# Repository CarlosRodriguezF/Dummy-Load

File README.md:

# Dummy-Load
Dummy-Load with Digital Control

V1.1
-----------------
1. Serie Resistor on MOSFET GATE to prevent oscillators.
2. NEW OPAMP RailtoRail DUAL, LMC662
3. New desing of PCB

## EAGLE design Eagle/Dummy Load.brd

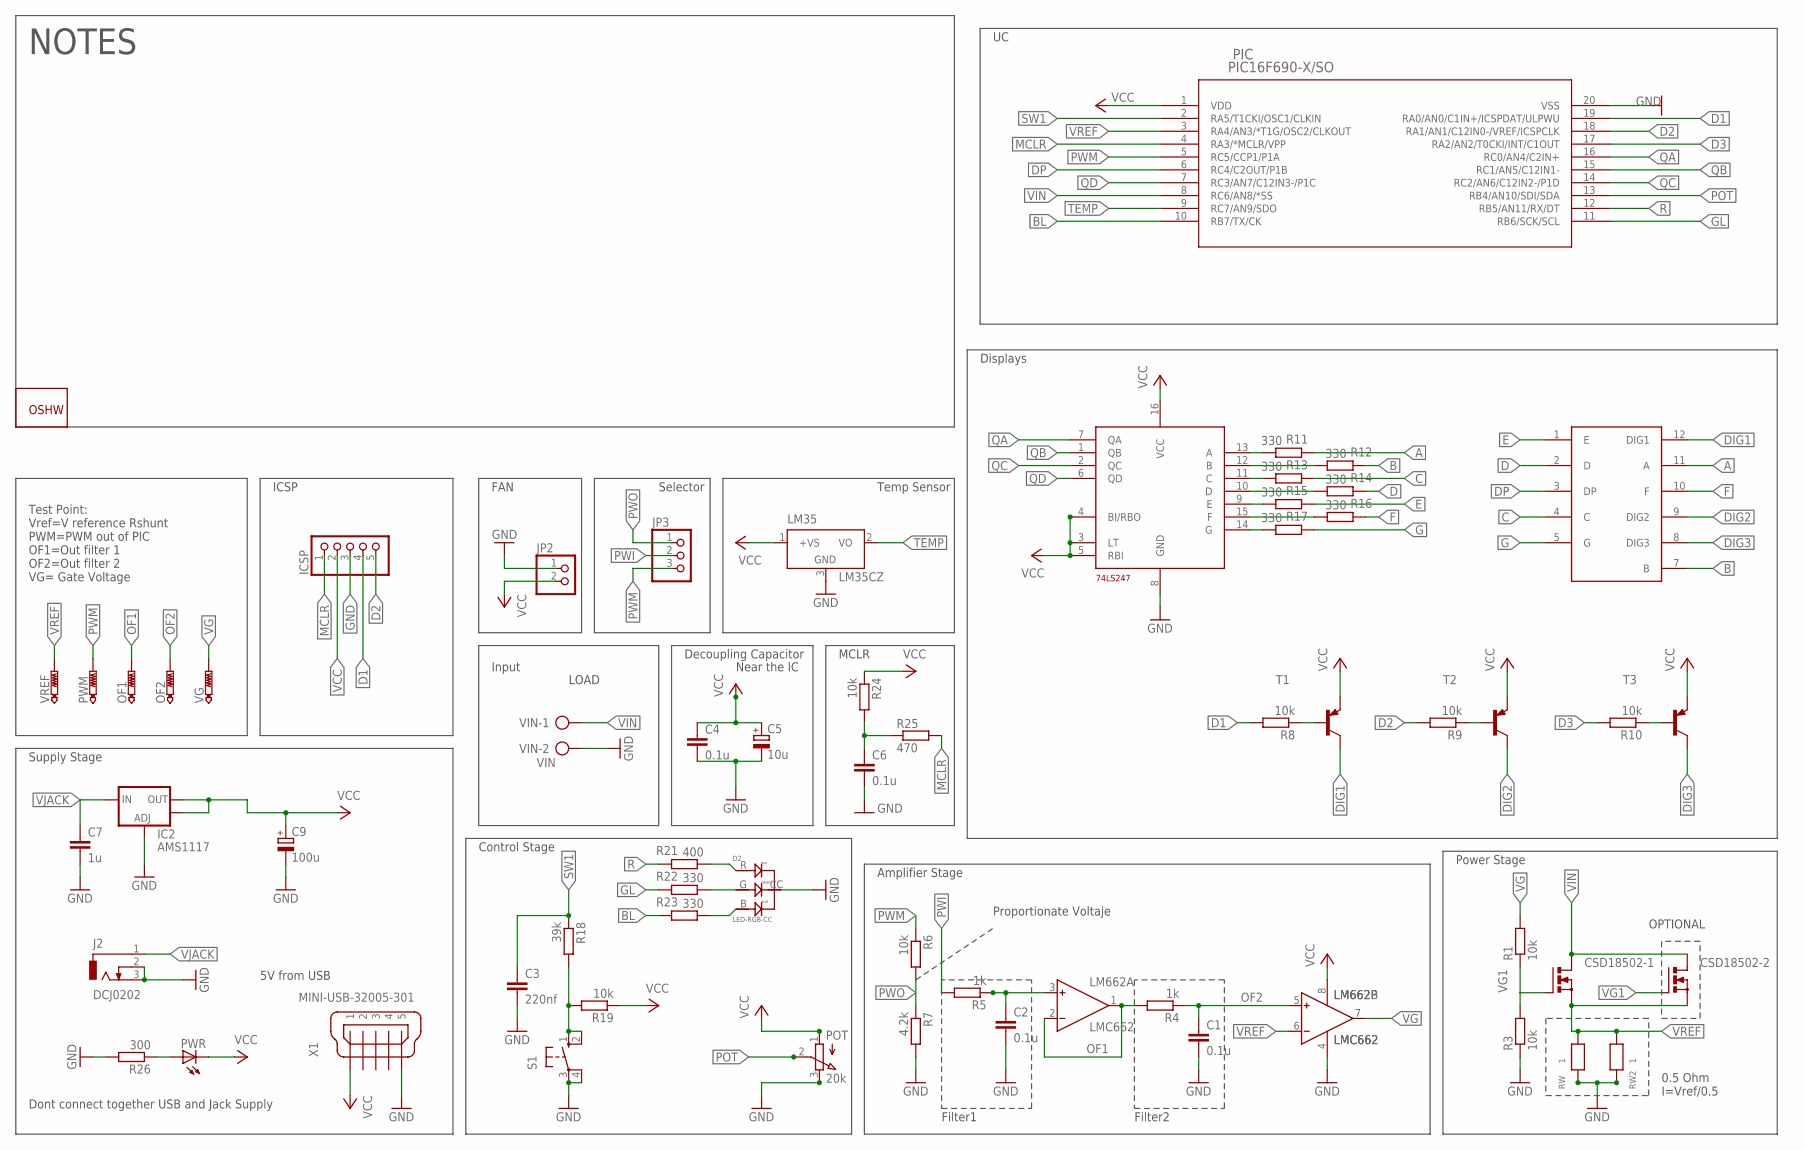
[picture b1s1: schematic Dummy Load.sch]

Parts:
74LS247: BCD-7; SOIC-16
C1, C2, C4, C6: 0.1u; C0805
C3: 220nf; C0805
C5: 10u; 153CLV-0405
C7: 1u; C0805
C9: 100u; 153CLV-0605
CSD18502-1, CSD18502-2: PMOSFET_NTO220BV; TO220BV
D2: LED-RGB-CC
DISPLAY: 7-SEGMENT--DIGITS
GOLD_ORB_SM2: OSHWLOGO_GOLD_ORB_MED; OSHW1
IC2: AMS1117; SOT223
ICSP: PINHD-1X5; 1X05
J2: DCJ0202
JP2: PINHD-1X2; 1X02
JP3: PINHD-1X3; 1X03
LM35: LM35CZ; TO92
LM662: LMC662; SO8
OF1, OF2: PTR1B1,27; B1,27
PIC: PIC16F690-X/SO; SOIC20-W_MC
POT: 20k; 3RP/1610N
PWM: PTR1B1,27; B1,27
PWR: LEDCHIP-LED0805; CHIP-LED0805
R1, R3, R6, R8, R9, R10, R19, R24: 10k; R0805
R4, R5: 1k; R0805
R7: 4.2k; R0805
R11, R12, R13, R14, R15, R16, R17, R22, R23: 330; R0805
R18: 39k; R0805
R21: 400; R0805
R25: 470; R0805
R26: 300; R0805
RW, RW2: 1; RESISTOR5W
S1: 10-XX; B3F-10XX
T1, T2, T3: MMBT540LT1-PNP-SOT23-BEC; SOT23-BEC
VG: PTR1B1,27; B1,27
VIN: VIN; AK500/2-H
VREF: PTR1B1,27; B1,27
X1: MINI-USB-32005-301; 32005-301

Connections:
A: DISPLAY.11 (A), R11.1
B: DISPLAY.7 (B), R12.1
BL: PIC.10 (RB7/TX/CK), R23.2
C: DISPLAY.4 (C), R13.1
D: DISPLAY.2 (D), R14.1
D1: ICSP.4, PIC.19 (RA0/AN0/C1IN+/ICSPDAT/ULPWU), R8.2
D2: ICSP.5, PIC.18 (RA1/AN1/C12IN0-/VREF/ICSPCLK), R9.2
D3: PIC.17 (RA2/AN2/T0CKI/INT/C1OUT), R10.2
DIG1: DISPLAY.12 (DIG1), T1.C
DIG2: DISPLAY.9 (DIG2), T2.C
DIG3: DISPLAY.8 (DIG3), T3.C
DP: DISPLAY.3 (DP), PIC.6 (RC4/C2OUT/P1B)
E: DISPLAY.1 (E), R15.1
F: DISPLAY.10 (F), R16.1
G: DISPLAY.5 (G), R17.1
GL: PIC.11 (RB6/SCK/SCL), R22.2
GND: 74LS247.8 (GND), C1.2, C2.2, C3.2, C4.2, C5.-, C6.2, C7.2, C9.-, D2.CC, IC2.1 (ADJ), ICSP.3, J2.2, J2.3, JP2.1, LM35.3 (GND), LM662.4 (V-), PIC.20 (VSS), POT.3 (E), R3.1, R7.2, R26.2, RW.P$1 (1), RW2.P$1 (1), S1.3, S1.4 (P1), VIN.2, X1.5
MCLR: ICSP.1, PIC.4 (RA3/*MCLR/VPP), R25.2
unnamed: PWR.A, R26.1
unnamed: R8.1, T1.B
unnamed: R10.1, T3.B
unnamed: C2.1, LM662.3 (IN+), R5.1
unnamed: R9.1, T2.B
unnamed: 74LS247.13 (A), R11.2
unnamed: 74LS247.12 (B), R12.2
unnamed: 74LS247.11 (C), R13.2
unnamed: 74LS247.10 (D), R14.2
unnamed: 74LS247.9 (E), R15.2
unnamed: 74LS247.15 (F), R16.2
unnamed: 74LS247.14 (G), R17.2
unnamed: R18.2, R19.2, S1.1 (S), S1.2 (S1)
unnamed: D2.R, R21.1
unnamed: D2.G, R22.1
unnamed: D2.B, R23.1
unnamed: C6.1, R24.2, R25.1
OF1: LM662.1 (OUT), LM662.2 (IN-), OF1.TP, R4.2
OF2: C1.1, LM662.5 (IN+), OF2.TP, R4.1
POT: PIC.13 (RB4/AN10/SDI/SDA), POT.2 (S)
PWI: JP3.2, R5.2
PWM: JP3.3, PIC.5 (RC5/CCP1/P1A), PWM.TP, R6.1
PWO: JP3.1, R6.2, R7.1
QA: 74LS247.7 (QA), PIC.16 (RC0/AN4/C2IN+)
QB: 74LS247.1 (QB), PIC.15 (RC1/AN5/C12IN1-)
QC: 74LS247.2 (QC), PIC.14 (RC2/AN6/C12IN2-/P1D)
QD: 74LS247.6 (QD), PIC.7 (RC3/AN7/C12IN3-/P1C)
R: PIC.12 (RB5/AN11/RX/DT), R21.2
SW1: C3.1, PIC.2 (RA5/T1CKI/OSC1/CLKIN), R18.1
TEMP: LM35.2 (VO), PIC.9 (RC7/AN9/SDO)
VCC: 74LS247.3 (LT), 74LS247.4 (BI/RBO), 74LS247.5 (RBI), 74LS247.16 (VCC), C4.1, C5.+, C9.+, IC2.2 (OUT), IC2.4 (OUT), ICSP.2, JP2.2, LM35.1 (+VS), LM662.8 (V+), PIC.1 (VDD), POT.1 (A), PWR.C, R19.1, R24.1, T1.E, T2.E, T3.E, X1.1
VG: LM662.7 (OUT), R1.2, VG.TP
VG1: CSD18502-1.G, CSD18502-2.G, R1.1, R3.2
VIN: CSD18502-1.D, CSD18502-2.D, PIC.8 (RC6/AN8/*SS), VIN.1
VJACK: C7.1, IC2.3 (IN), J2.1
VREF: CSD18502-1.S, CSD18502-2.S, LM662.6 (IN-), PIC.3 (RA4/AN3/*T1G/OSC2/CLKOUT), RW.P$2 (2), RW2.P$2 (2), VREF.TP

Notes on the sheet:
Power Stage
Amplifier Stage
Filter1
Filter2
Displays
0.5 Ohm I=Vref/0.5
OPTIONAL
Proportionate Voltaje
Control Stage
5V from USB
Decoupling Capacitor
Near the IC
MCLR
Input
Dont connect together USB and Jack Supply
LOAD
Test Point: Vref=V reference Rshunt PWM=PWM out of PIC OF1=Out filter 1 OF2=Out filter 2 VG= Gate Voltage
Temp Sensor
ICSP
FAN
NOTES
Selector
Supply Stage

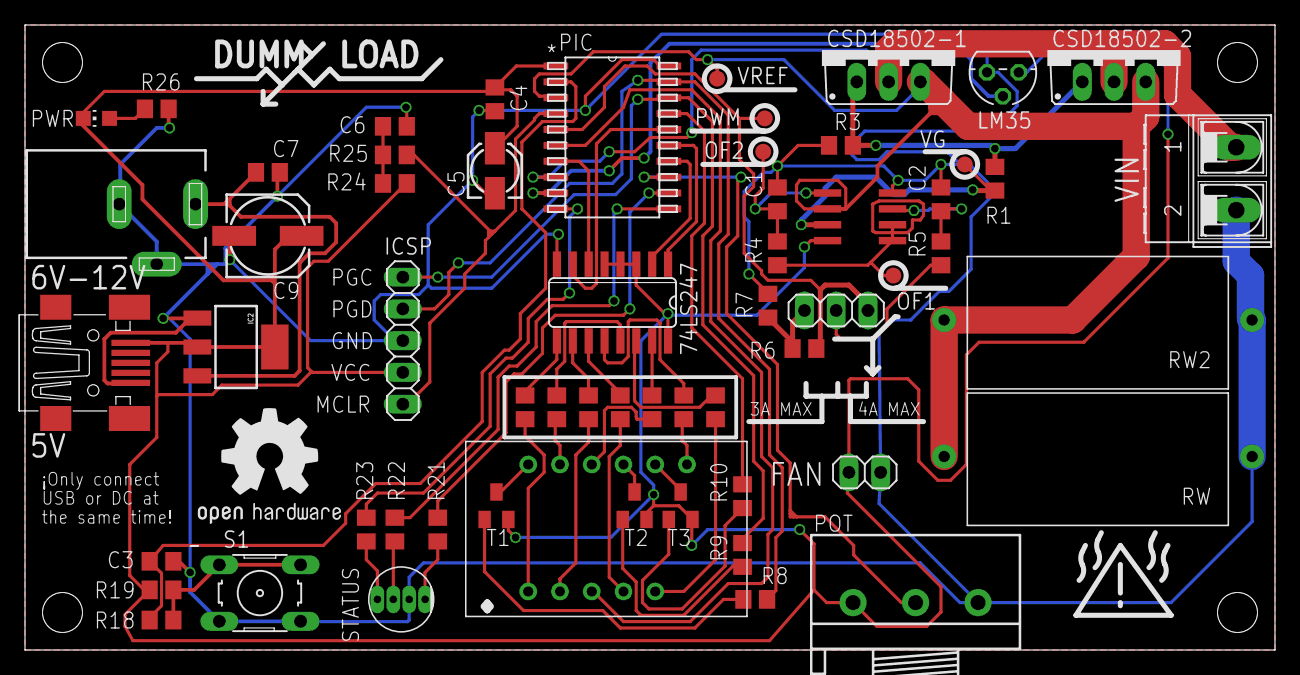
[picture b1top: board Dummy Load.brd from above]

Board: 2 copper layers, 100.0 x 50.0 mm, 61 parts (0 on the bottom side), 54 nets.

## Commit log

2015-02-18 :neckbeard: Added .gitattributes & .gitignore files
2015-02-18 Files V1
    Upload Files V1
2015-02-20 Upload Latest Version
    Upload Pre-Finished Version of SCH and BOARD
2015-02-20 Preview V1
2015-02-21 Update Proteus Files & Latest BRD Version
2015-02-26 Update all files to V1.1
    Implement Gate Series Resistor on MOSFET, to prevent the oscillators in
    the output. Also implement new OPAMP LMC662, and new desing of PCB

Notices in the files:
parts and their libraries:
SparkFun-PowerIC: Licensing: Creative Commons ShareAlike 4.0 International - https://creativecommons.org/licenses/by-sa/4.0
